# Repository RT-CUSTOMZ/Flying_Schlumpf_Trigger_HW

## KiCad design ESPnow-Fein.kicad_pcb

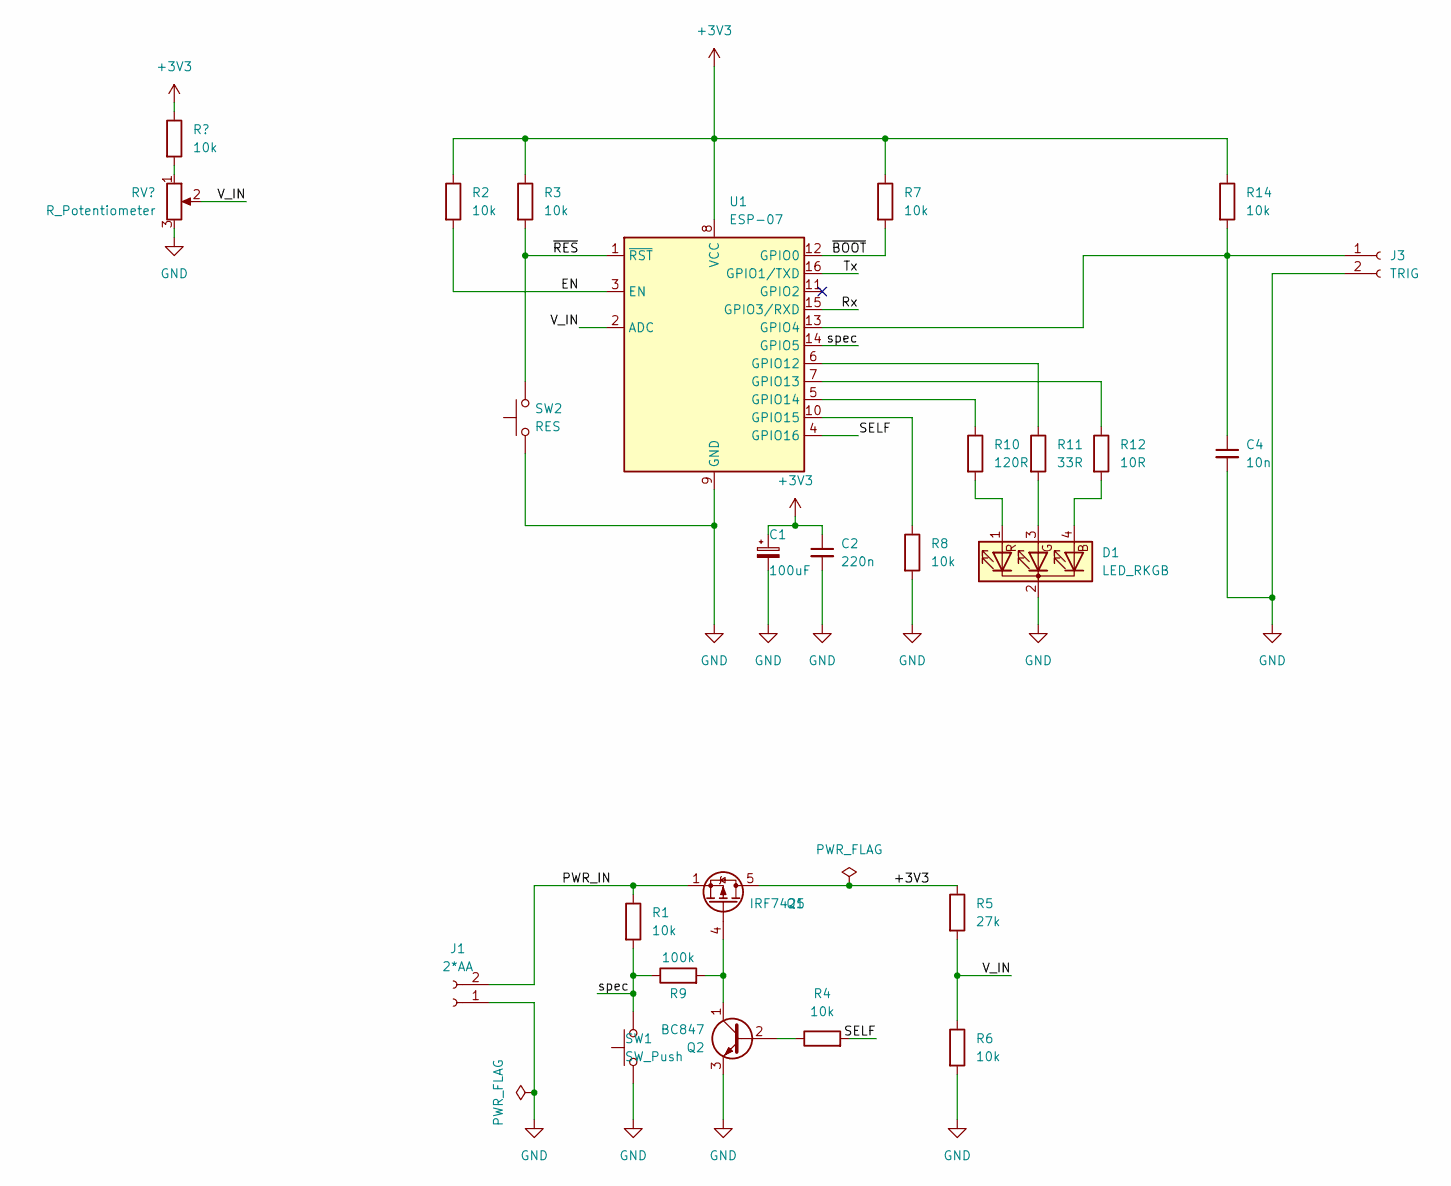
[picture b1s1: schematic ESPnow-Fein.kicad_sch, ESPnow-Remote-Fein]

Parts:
C1: 100uF; CP_Elec_6.3x3
C2: 220n; C_0805_2012Metric_Pad1.18x1.45mm_HandSolder
C4: 10n; C_0805_2012Metric_Pad1.18x1.45mm_HandSolder
D1: LED_RKGB; LED_D5.0mm-4_RGB
J1: 2*AA; PinHeader_1x02_P2.54mm_Vertical
J3: TRIG; TerminalBlock_bornier-2_P5.08mm
Q1: IRF7425; SO-8_5.3x6.2mm_P1.27mm
Q2: BC847; SOT-23
R1, R2, R3, R4, R6, R7, R8, R14: 10k; R_0805_2012Metric_Pad1.20x1.40mm_HandSolder
R5: 27k; R_0805_2012Metric_Pad1.20x1.40mm_HandSolder
R9: 100k; R_0805_2012Metric_Pad1.20x1.40mm_HandSolder
R10: 120R; R_0805_2012Metric_Pad1.20x1.40mm_HandSolder
R11: 33R; R_0805_2012Metric_Pad1.20x1.40mm_HandSolder
R12: 10R; R_0805_2012Metric_Pad1.20x1.40mm_HandSolder
SW1: SW_Push; Push_E-Switch_KS01Q01
SW2: RES; SW_PUSH_6mm_H4.3mm
U1: ESP-07; ESP-07_tht

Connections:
+3V3: C1.1, C2.1, Q1.5 (D), Q1.6 (D), Q1.7 (D), Q1.8 (D), R2.1, R3.1, R5.1, R7.1, R14.1, U1.8 (VCC); also elsewhere on the board
/EN: R2.2, U1.3 (EN)
/PWR_IN: J1.2, Q1.1 (D), Q1.2 (S), Q1.3 (D), R1.1
/Rx: U1.15 (GPIO3/RXD)
/SELF: R4.2, U1.4 (GPIO16)
/Tx: U1.16 (GPIO1/TXD)
/V_IN: R5.2, R6.1, U1.2 (ADC)
/spec: R1.2, R9.1, SW1.2, SW1.4 (2), U1.14 (GPIO5)
/~BOOT: R7.2, U1.12 (GPIO0)
/~RES: R3.2, SW2.2, U1.1 (~RST)
GND: C1.2, C2.2, C4.2, D1.2 (K), J1.1, J3.2, Q2.3 (E), R6.2, R8.2, SW1.1, SW1.3 (1), SW2.1, U1.9 (GND); also elsewhere on the board
unnamed: C4.1, J3.1, R14.2, U1.13 (GPIO4)
unnamed: Q1.4 (G), Q2.1 (C), R9.2
unnamed: Q2.2 (B), R4.1
unnamed: R8.1, U1.10 (GPIO15)
unnamed: R10.1, U1.5 (GPIO14)
unnamed: D1.1 (RA), R10.2
unnamed: R11.1, U1.6 (GPIO12)
unnamed: D1.3 (GA), R11.2
unnamed: D1.4 (BA), R12.2
unnamed: R12.1, U1.7 (GPIO13)

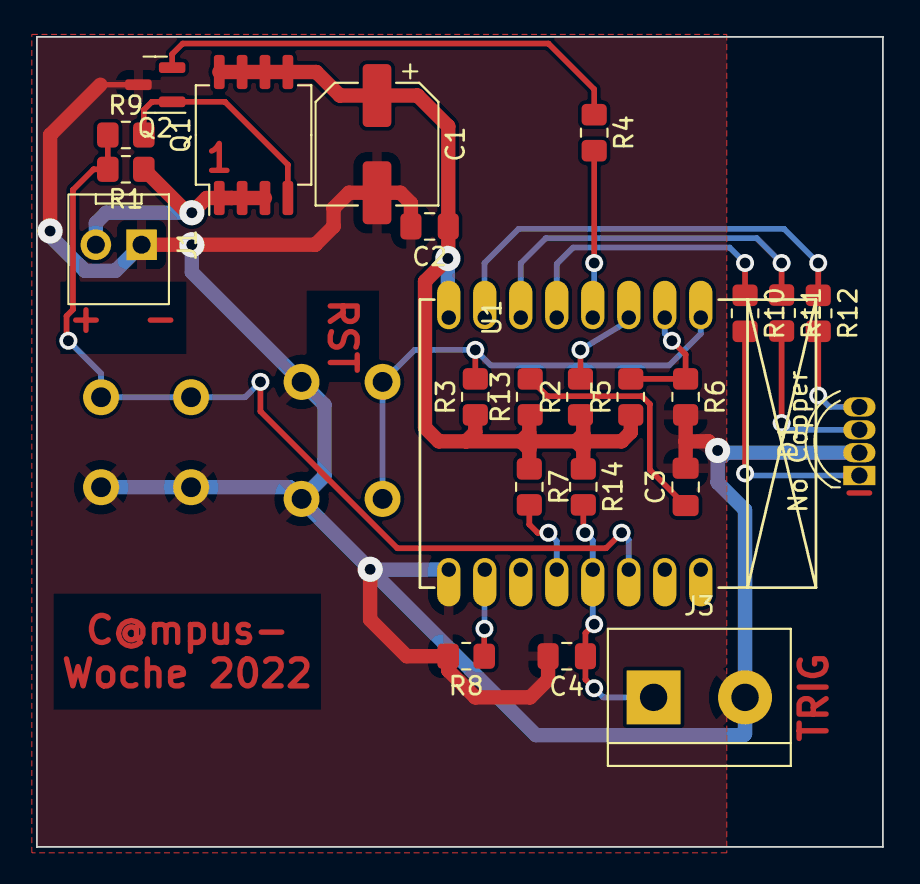
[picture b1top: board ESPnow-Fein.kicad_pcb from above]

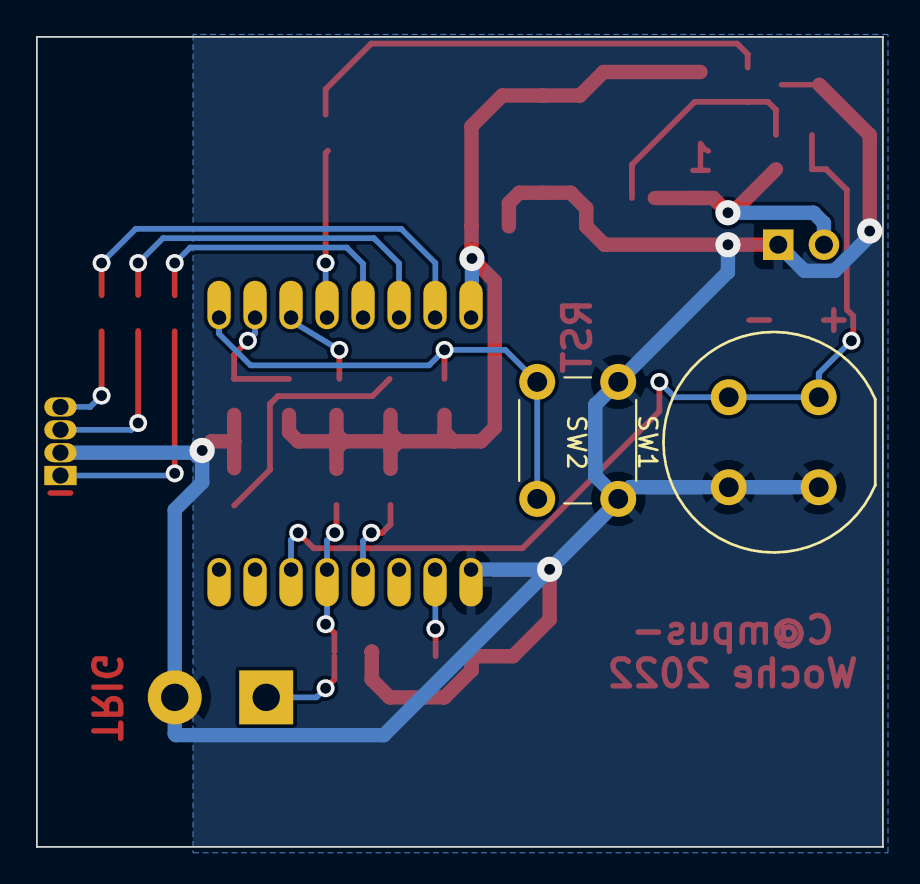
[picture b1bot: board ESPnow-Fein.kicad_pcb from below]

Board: 2 copper layers, 47.0 x 45.0 mm, 26 parts (2 on the bottom side), 20 nets.

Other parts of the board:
C3: 10n; C_0805_2012Metric_Pad1.18x1.45mm_HandSolder
R13: 10k; R_0805_2012Metric_Pad1.20x1.40mm_HandSolder

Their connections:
+3V3: R13.1; also elsewhere on the board
GND: C3.2; also elsewhere on the board
unnamed: C3.1, R13.2

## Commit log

2022-12-22 First Commit
    Commit of Project after CW22
